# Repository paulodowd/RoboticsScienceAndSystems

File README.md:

# SLAMDunk

Fork of the University of Bristol MSc Robotics "Robotics Science and Systems"
unit repository, containing the digital twin simulation platform and StampC3
robot template code used for coursework/labs on the module, plus our own
tooling for logging and benchmarking the robot.

Course guide: <https://semtm0043-42.github.io/getting-started.html>

## Repository layout

| Path | What it is |
|---|---|
| `StampC3_Template/` | Arduino sketch for the M5Stack StampC3 that controls the Pololu 3Pi+ over I2C and streams telemetry over WiFi |
| `DigitalTwin/` | Processing sketch: simulated robot, live comparison with the real robot |
| `tools/logger.py` | Python telemetry logger: live terminal dashboard and Rerun visualisation |
| `logs/` | Local captures (ignored by git) |
| `TODO.md` | Benchmarking plan for the final project |

## System overview

```
Pololu 3Pi+ (ATmega32U4, course middleware)
        │ I2C, address 0x08
M5Stack StampC3 (ESP32-C3) ── runs StampC3_Template
        │ WiFi access point, TCP 192.168.4.1:80, one client at a time
Laptop ── tools/logger.py  or  DigitalTwin
```

The robot sends one CSV line every 50 ms, in this order (see `StampC3_Template/Controller.h`):

```
t_ms, x_mm, y_mm, theta_rad, pwm_left, pwm_right, enc_left, enc_right, dn1, dn2, dn3, dn4, dn5, signal
```

`t_ms` is the StampC3's uptime. x, y and theta come from the StampC3's own
odometry. dn1–dn5 are the surface sensors. The line thresholds for each sensor should ideally be tuned individually for each individual robot. `signal` is 0 while waiting and 1 once the button has
started the controller.

---

## 1. Robot setup (Arduino)

**All of these instructions can also be found in the course guide (Link above or in your course blackboard). Treat this as distilled information from the course guide.**

### Arduino IDE

Install Arduino IDE 2.x from <https://www.arduino.cc/en/software>.

On Linux, use the **AppImage**, not the snap. The snap is sandboxed and cannot
open files outside your home folder (for example, a repo under `/data`).

```bash
chmod +x arduino-ide_*_Linux_64bit.AppImage
./arduino-ide_*_Linux_64bit.AppImage
```

If it fails to start with a FUSE error, run `sudo apt install libfuse2`.

For macOS and Windows check the course guide for instructions.

### Board package and libraries

1. **File → Preferences → Additional boards manager URLs**, add:
   ```
   https://static-cdn.m5stack.com/resource/arduino/package_m5stack_index.json
   ```
2. **Tools → Board → Boards Manager**: search `M5Stack` and install it.
3. **Tools → Manage Libraries**: install `LSM6` and `LIS3MDL` (both by Pololu).

### Flashing

1. Open `StampC3_Template/StampC3_Template.ino`.
2. Tools settings:
   - **Board:** M5Stack Arduino → **M5StampC3**
   - **USB CDC On Boot:** **Disabled** (otherwise the Serial Monitor shows nothing)
   - **Upload Speed:** 921600, or 115200 if uploads fail
3. **Set a unique WiFi name and password** on this line of the sketch:
   ```cpp
   RobotWifiAP_c server("myAP", "myPassword", 80);
   ```
   Every robot running the template broadcasts `myAP` by default, so in a lab
   you could end up connected to someone else's robot.
4. Upload, then turn the 3Pi+ on with its power button.

The Serial Monitor runs at **115200 baud** and shows the same CSV lines as WiFi.

### Serial port access (Linux)

Your user must be in the `dialout` group to upload over USB:

```bash
sudo usermod -aG dialout $USER     # then log out and back in
```

### Batteries

Use 4 × AA NiMH cells, fully charged; wait until every charger channel shows
green. **Motor speed at a fixed PWM drops as the batteries run down, which
affects tuning and odometry. Note the charge state in any benchmark.**

---

## 2. Digital Twin (Processing)

1. Install Processing 4 from <https://processing.org/download>.
2. Open `DigitalTwin/DigitalTwin.pde`.
3. Run it. It works standalone as a simulator. For live comparison it connects
   to the robot at `192.168.4.1:80` (set in `DigitalTwin/Simulator.pde`).

The robot serves only **one TCP client**, so the Digital Twin and the logger
cannot both be connected over WiFi at the same time.

---

## 3. Telemetry logger (`tools/logger.py`)

### Install

The logger needs **Python 3.10 or newer** and two packages:

- `rich` draws the live terminal dashboard.
- `rerun-sdk` includes the Rerun viewer (the `rerun` command). Tested with
  rerun-sdk 0.27.2. Rerun's API changes between releases, so if a newer
  version breaks something, install that version instead: `rerun-sdk==0.27.2`.

Install them in a **virtual environment** (`.venv`, a private folder of
packages for this project). Newer Linux distributions and Homebrew Python
refuse `pip install` outside one, and it keeps the versions separate from
the rest of your system. Run these from the repo's root folder.

#### Linux (Ubuntu/Debian)

```bash
sudo apt install python3 python3-venv python3-pip
python3 -m venv .venv
source .venv/bin/activate
pip install rich rerun-sdk
```

#### macOS

Install Python 3 from <https://www.python.org/downloads/> or with Homebrew
(`brew install python`). The `python3` that comes with Xcode's command line
tools may be older than 3.10; check with `python3 --version`.

```bash
python3 -m venv .venv
source .venv/bin/activate
pip install rich rerun-sdk
```

#### Windows

Install Python 3 from <https://www.python.org/downloads/> and tick
**"Add python.exe to PATH"** in the installer, or run
`winget install Python.Python.3.12`. Use Windows Terminal (PowerShell) so the
dashboard draws correctly.

```powershell
py -m venv .venv
.venv\Scripts\Activate.ps1
pip install rich rerun-sdk
```

If PowerShell refuses to run `Activate.ps1`, allow local scripts once with
`Set-ExecutionPolicy -Scope CurrentUser RemoteSigned`, then try again. In
Command Prompt (cmd) the activate command is `.venv\Scripts\activate.bat`.

#### Check the install

With the virtual environment active (your prompt starts with `(.venv)`):

```bash
python -c "import rich, rerun; print('ok', rerun.__version__)"
```

Activate the environment again (`source .venv/bin/activate`, or
`.venv\Scripts\Activate.ps1` on Windows) in each new terminal before running
the logger. `.venv/` is ignored by git.

### Connect to the robot

The robot is its own WiFi network. Join it with the name and password you set
in the sketch. While connected, your computer has no internet over WiFi.

You can connect to the the robot like you connect to a normal wifi network, or follow the commands below to connect from terminal.

**Linux:**

```bash
nmcli dev wifi connect <robot-ssid> password <robot-password>
```

To stop NetworkManager switching back to a network with internet in the
middle of a run, give the robot's network priority:

```bash
nmcli con modify <robot-ssid> connection.autoconnect-priority 100
```

**macOS:** choose the network from the WiFi menu in the menu bar, or:

```bash
networksetup -setairportnetwork en0 <robot-ssid> <robot-password>
```

(`en0` is the WiFi interface on most Macs; `networksetup -listallhardwareports`
shows yours.) macOS may warn that the network has no internet connection;
stay connected anyway.

**Windows:** choose the network from the WiFi icon in the taskbar. When
Windows reports "No internet", stay connected anyway. If Windows asks whether
to allow Python or Rerun through the firewall, allow it on private networks.

**Check that data is arriving** (all platforms, `Ctrl+C` to stop):

```bash
python -c "import socket; s=socket.create_connection(('192.168.4.1',80)); [print(d.decode(), end='') for d in iter(lambda: s.recv(4096), b'')]"
```

On Linux and macOS, `nc 192.168.4.1 80` does the same.

### Run

Settings are constants at the top of `tools/logger.py`:

| Constant | Robot | Local test | Meaning |
|---|---|---|---|
| `HOST` | `"192.168.4.1"` | `"127.0.0.1"` | Address to connect to |
| `PORT` | `80` | `9000` | TCP port |
| `TIMEOUT_S` | `3` | `3` | Seconds of silence before giving up |
| `USE_RERUN` | `True` | `True` | Open the Rerun viewer |

Then, with the virtual environment active:

```bash
python tools/logger.py            # Linux, macOS
```

```powershell
python tools\logger.py            # Windows
```

Stop it with **Ctrl+C**.

The first time the Rerun viewer opens, macOS or Windows may ask whether to
allow incoming network connections. Allow it: the logger sends data to the
viewer over a local network port.

### What you see

**Terminal:** a table of the latest record with every field labelled, updated
about 10 times a second. Warnings and errors are printed above the table.

**Rerun viewer** (opens automatically when `USE_RERUN = True`):

| Panel | Shows |
|---|---|
| Path | The robot's trail and a heading arrow (odometry x, y, theta) |
| Pose | x, y, theta over time |
| Motor PWM | Commanded left and right PWM |
| Encoders | Left and right encoder counts |
| Surface sensors | dn1–dn5 over time |
| Surface now | Bar chart of the current dn1–dn5 |

Notes on the viewer:

- The time axis is the robot's own clock (`robot_time`), so WiFi delays don't
  distort the plots. Drag the time cursor to scrub back through a run.
- The Path view draws y flipped, because Rerun's 2D +y points down and the
  robot's +y is anticlockwise (up). The Pose plots show the true y.
- If a viewer is already open, the logger adds a new recording to it rather
  than opening a second window. Pick recordings from the list on the left.
- After a robot reset, `t_ms` restarts near 0, so the new data is drawn over
  the old run on the same timeline.
- Without a display (for example, over SSH) the viewer cannot open. Set
  `USE_RERUN = False`.

### Log messages

| Message | Meaning |
|---|---|
| `not on the robot's WiFi` | The laptop has no route to 192.168.4.1. Join the robot's network. |
| `Server not listening. Robot must be booting.` | Something answered, but nothing is listening on the port. Wait for the robot to finish booting, or check `nc` is running for a local test. |
| `robot did not answer within 3 s` | No answer to the connection at all: robot off or out of range. |
| `no data for 3 s` | Connected, but the data stopped: robot reset, out of range, laptop left the network, or another client holds the connection. |
| `connection ended: Closed by the server.` | The other side closed the connection normally. |
| `expected 14 fields, got N` / `not a number` | A line that isn't a telemetry record was received and skipped. |
| `discarding incomplete last line` | The connection ended partway through a line. |

### Test without the robot

The logger can be tested entirely on your computer, using a saved capture and
a small server pretending to be the robot. No robot or robot WiFi is needed.
These commands work on Linux, macOS and Windows (on Windows, use `\` instead of
`/` in the file paths if a command can't find the file).

1. Record a capture once, while connected to the robot. Press `Ctrl+C` after a
   few seconds; the traceback it prints is expected.
   ```bash
   python -c "import socket; s=socket.create_connection(('192.168.4.1',80)); f=open('logs/capture.csv','wb'); [f.write(d) for d in iter(lambda: s.recv(4096), b'')]"
   ```
2. Set `HOST = "127.0.0.1"` and `PORT = 9000` in `tools/logger.py`.
3. In one terminal, serve the capture:
   ```bash
   python -c "import socket,sys; s=socket.create_server(('127.0.0.1',9000)); c,_=s.accept(); c.sendall(open(sys.argv[1],'rb').read()); c.close()" logs/capture.csv
   ```
4. In another terminal, run the logger:
   ```bash
   python tools/logger.py
   ```

The server exits after one connection, so rerun step 3 before each test. It
closes the connection after sending the file, so the logger should end with
`connection ended: Closed by the server.`

On Linux, `nc` does the same jobs: `nc 192.168.4.1 80 | tee logs/capture.csv`
to record, and `nc -N -l 9000 < logs/capture.csv` to serve (`-N` closes the
connection at the end of the file).

### Current limitations

- **Records are not saved to disk yet.** The dashboard and Rerun show live data
  only. Writing to CSV is the next step. Until then, record a raw capture as
  in step 1 of "Test without the robot".
- **No automatic reconnect.** The logger exits when the connection drops.
  Restart it after the robot resets.
- **One client at a time.** While the logger is connected, the Digital Twin
  (or a second logger) will connect but receive nothing.

---

## Troubleshooting

| Problem | Fix |
|---|---|
| Arduino IDE can't see the repo folder | You're using the snap version. Install the AppImage (see above). |
| Serial Monitor is blank | Set **USB CDC On Boot → Disabled** and re-upload; check the baud rate is 115200. |
| Upload fails or port not found | Add yourself to `dialout`; try Upload Speed 115200. |
| Robot doesn't turn on | Press the 3Pi+ power button; check the cells' orientation and charge. |
| Robot's WiFi doesn't appear | Robot is off, still booting, or the sketch isn't flashed. |
| Logger connects, then exits with `no data for 3 s` | Another client (Digital Twin, `nc`, another logger) may hold the connection. Close it, wait a few seconds, and try again. |
| `ModuleNotFoundError: rich` or `rerun` | The virtual environment isn't active in this terminal. Activate it (see Install), or install the packages into it. |
| `error: externally-managed-environment` from pip | You ran pip outside the virtual environment. Create and activate `.venv` first (see Install). |
| Windows: `python` opens the Microsoft Store or isn't found | Use `py` instead of `python`, or reinstall Python with "Add python.exe to PATH" ticked. |
| Windows: `Activate.ps1 cannot be loaded` | Run `Set-ExecutionPolicy -Scope CurrentUser RemoteSigned` once in PowerShell. |
| Logger says `robot did not answer` instead of `not on the robot's WiFi` | Normal on some systems when you aren't on the robot's network: the connection times out instead of failing straight away. Check which WiFi you're on. |
| Rerun viewer doesn't open (macOS/Windows) | Allow the firewall or "incoming connections" prompt, then run the logger again. |

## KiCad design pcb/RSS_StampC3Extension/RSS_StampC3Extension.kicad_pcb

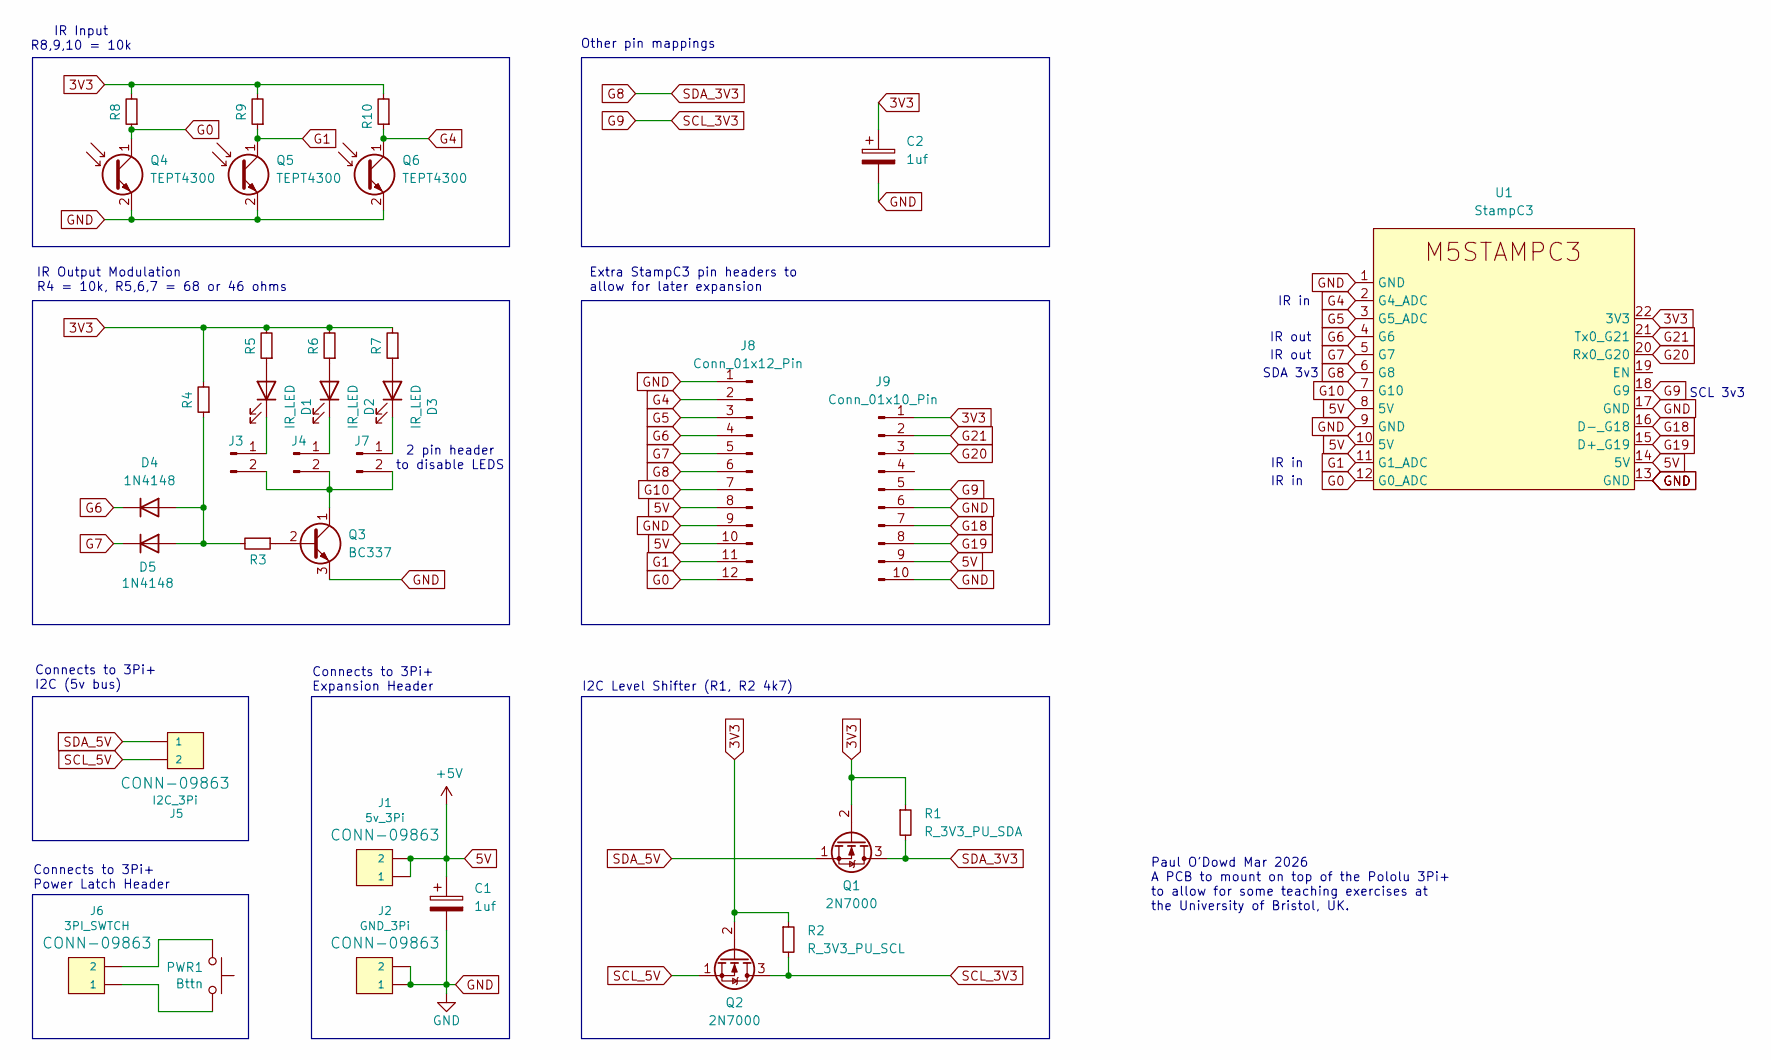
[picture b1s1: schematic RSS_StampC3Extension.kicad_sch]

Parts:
C1, C2: 1uf; CP_Radial_D5.0mm_P2.00mm
D1, D2, D3: IR_LED; LED_D3.0mm_Horizontal_O1.27mm_Z2.0mm
D4, D5: 1N4148; D_DO-35_SOD27_P7.62mm_Horizontal
J1: 5v_3Pi; PinHeader_1x02_P2.54mm_Vertical
J2: GND_3Pi; PinHeader_1x02_P2.54mm_Vertical
J3, J4, J7: PinHeader_1x02_P2.54mm_Vertical
J5: I2C_3Pi; PinHeader_1x02_P2.54mm_Vertical
J6: 3PI_SWTCH; PinHeader_1x02_P2.54mm_Vertical
J8: Conn_01x12_Pin; PinHeader_1x12_P2.54mm_Vertical
J9: Conn_01x10_Pin; PinHeader_1x10_P2.54mm_Vertical
PWR1: Bttn; SW_PUSH_6mm
Q1, Q2: 2N7000; TO-92_Inline
Q3: BC337; TO-92_Inline
Q4, Q5, Q6: TEPT4300; LED_D3.0mm_Clear
R1: R_3V3_PU_SDA; R_Axial_DIN0207_L6.3mm_D2.5mm_P10.16mm_Horizontal
R2: R_3V3_PU_SCL; R_Axial_DIN0207_L6.3mm_D2.5mm_P10.16mm_Horizontal
R3, R4, R5, R6, R7, R8, R9, R10: R_Axial_DIN0207_L6.3mm_D2.5mm_P10.16mm_Horizontal
U1: StampC3; Stamp-C3

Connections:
3V3: C2.1, J9.1, Q1.2 (G), Q2.2 (G), R1.1, R2.1, R4.2, R5.2, R6.2, R7.2, R8.2, R9.2, R10.2, U1.22 (3V3)
5V: C1.1, J1.1, J1.2, J8.8, J8.10, J9.9, U1.8 (5V), U1.10 (5V), U1.14 (5V)
G0: J8.12, Q4.1 (C), R8.1, U1.12 (G0_ADC)
G1: J8.11, Q5.1 (C), R9.1, U1.11 (G1_ADC)
G4: J8.2, Q6.1 (C), R10.1, U1.2 (G4_ADC)
G5: J8.3, U1.3 (G5_ADC)
G6: D4.1 (K), J8.4, U1.4 (G6)
G7: D5.1 (K), J8.5, U1.5 (G7)
G8: J8.6, Q1.3 (D), R1.2, U1.6 (G8)
G9: J9.5, Q2.3 (D), R2.2, U1.18 (G9)
G10: J8.7, U1.7 (G10)
G18: J9.7, U1.16 (D-_G18)
G19: J9.8, U1.15 (D+_G19)
G20: J9.3, U1.20 (Rx0_G20)
G21: J9.2, U1.21 (Tx0_G21)
GND: C1.2, C2.2, J2.1, J2.2, J8.1, J8.9, J9.6, J9.10, Q3.3 (E), Q4.2 (E), Q5.2 (E), Q6.2 (E), U1.1 (GND), U1.9 (GND), U1.13 (GND), U1.17 (GND)
unnamed: D1.2 (A), R5.1
unnamed: D1.1 (K), J3.1
unnamed: D2.2 (A), R6.1
unnamed: D2.1 (K), J4.1
unnamed: D3.2 (A), R7.1
unnamed: D3.1 (K), J7.1
unnamed: D4.2 (A), D5.2 (A), R3.2, R4.1
unnamed: J3.2, J4.2, J7.2, Q3.1 (C)
unnamed: J6.1, PWR1.1
unnamed: J6.2, PWR1.2
unnamed: Q3.2 (B), R3.1
SCL_5V: J5.2, Q2.1 (S)
SDA_5V: J5.1, Q1.1 (S)

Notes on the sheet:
IR out
IR in
2 pin header to disable LEDS
Paul O'Dowd Mar 2026 A PCB to mount on top of the Pololu 3Pi+ to allow for some teaching exercises at the University of Bristol, UK.
IR Input R8,9,10 = 10k
I2C Level Shifter (R1, R2 4k7)
IR Output Modulation R4 = 10k, R5,6,7 = 68 or 46 ohms
Connects to 3Pi+ I2C (5v bus)
Extra StampC3 pin headers to allow for later expansion
Connects to 3Pi+ Expansion Header
SDA 3v3
SCL 3v3
Connects to 3Pi+ Power Latch Header
Other pin mappings

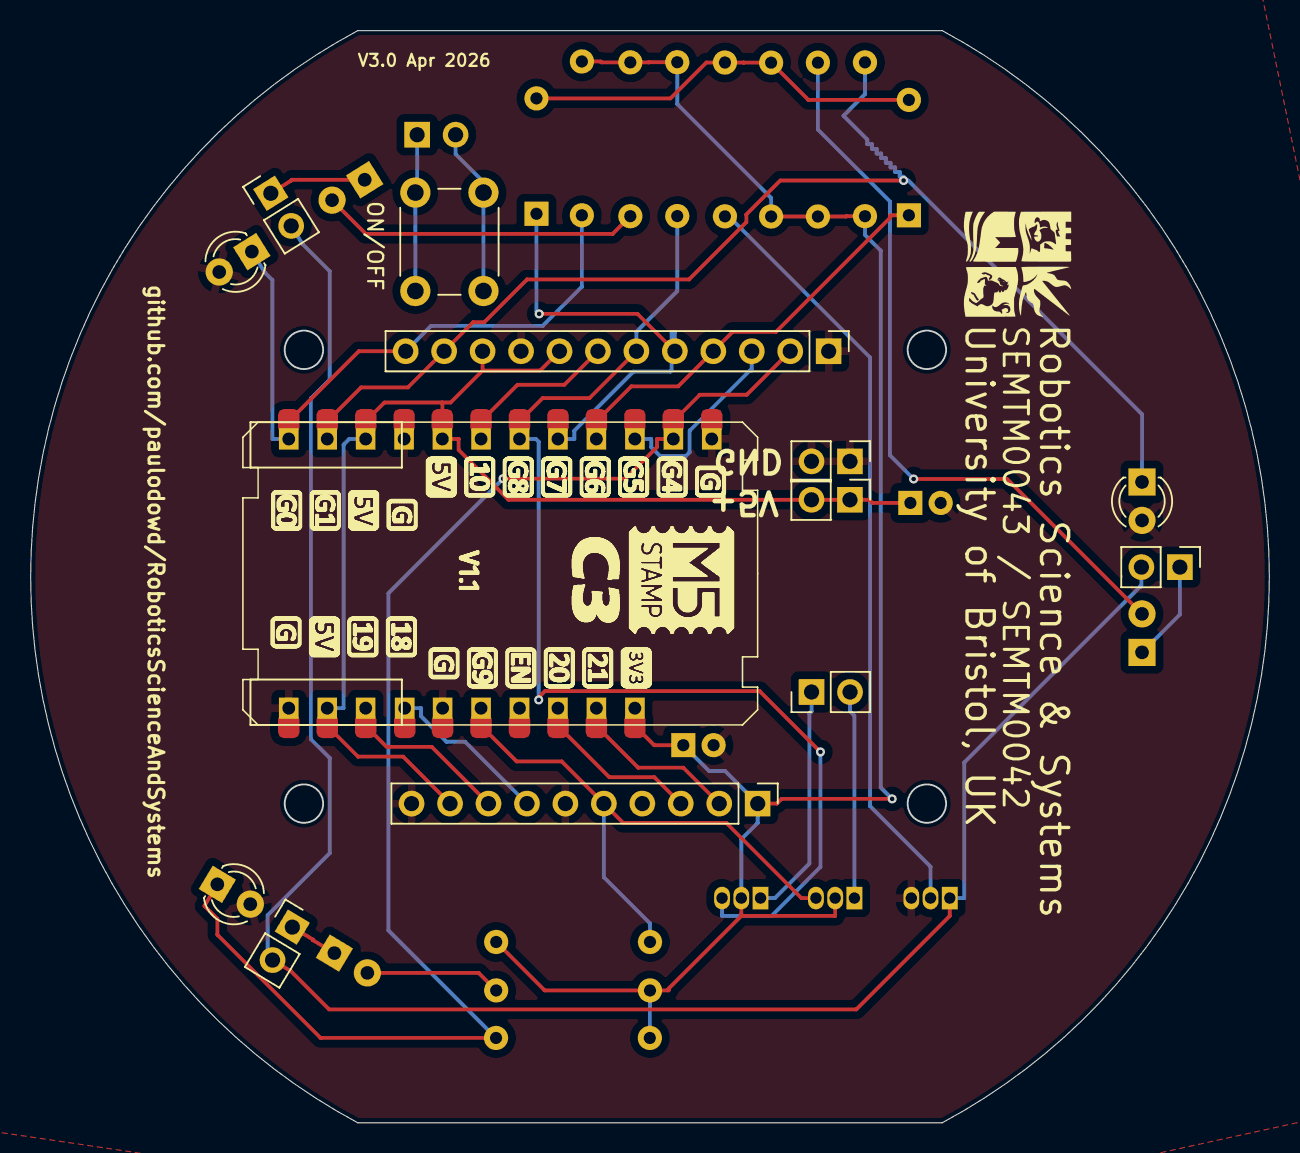
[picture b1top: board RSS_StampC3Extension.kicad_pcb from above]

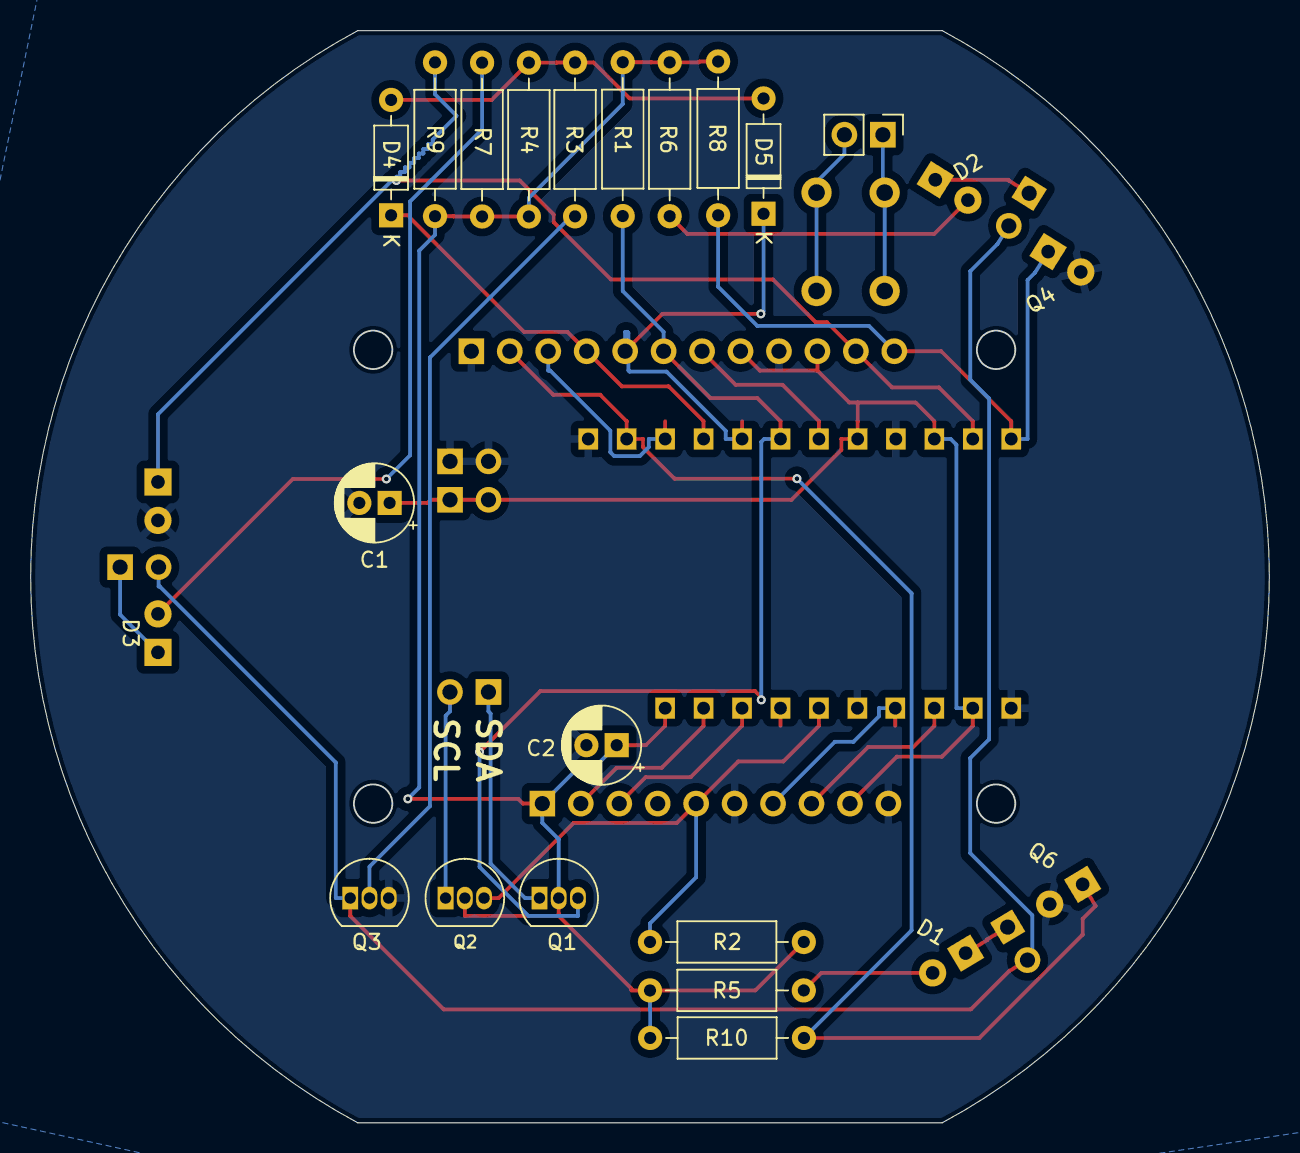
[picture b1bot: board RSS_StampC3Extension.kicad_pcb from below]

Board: 2 copper layers, 81.8 x 72.1 mm, 34 parts (18 on the bottom side), 29 nets.

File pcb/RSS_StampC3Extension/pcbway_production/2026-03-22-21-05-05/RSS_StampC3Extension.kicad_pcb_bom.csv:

Designator,Quantity,Value,Footprint,Package,MPN,DNP,Mount_Type,Description,Sim.Device,Sim.Pins,Field4
"D1, D2, D3",3,IR_LED,LED_D3.0mm_Horizontal_O1.27mm_Z2.0mm,,,,tht,,,,
"D4, D5",2,1N4148,D_DO-35_SOD27_P7.62mm_Horizontal,,,,tht,"100V 0.15A standard switching diode, DO-35",D,1=K 2=A,
J1,1,5v_3Pi,PinHeader_1x02_P2.54mm_Vertical,,,,tht,,,,CONN-09863
J2,1,GND_3Pi,PinHeader_1x02_P2.54mm_Vertical,,,,tht,,,,CONN-09863
J5,1,I2C_3Pi,PinHeader_1x02_P2.54mm_Vertical,,,,tht,,,,CONN-09863
J6,1,3PI_SWTCH,PinHeader_1x02_P2.54mm_Vertical,,,,tht,,,,CONN-09863
J8,1,Conn_01x12_Pin,PinHeader_1x12_P2.54mm_Vertical,,,,tht,,,,
J9,1,Conn_01x10_Pin,PinHeader_1x10_P2.54mm_Vertical,,,,tht,,,,
PWR1,1,Bttn,SW_PUSH_6mm,,,,tht,,,,
"Q1, Q2",2,2N7000,TO-92_Inline,,,,tht,,,,
Q3,1,BC337,TO-92_Inline,,,,tht,"0.8A Ic, 45V Vce, NPN Transistor, TO-92",,,
"Q4, Q5, Q6",3,TEPT4300,LED_D3.0mm_Clear,,,,tht,"Ambient Light Sensor, NPN Epitaxial Planar Phototransistor, T-1",,,
R1,1,R_3V3_PU_SDA,R_Axial_DIN0207_L6.3mm_D2.5mm_P10.16mm_Horizontal,,,,tht,,,,
"R10, R3, R4, R5, R6, R7, R8, R9",8,~,R_Axial_DIN0207_L6.3mm_D2.5mm_P10.16mm_Horizontal,,,,tht,,,,
R2,1,R_3V3_PU_SCL,R_Axial_DIN0207_L6.3mm_D2.5mm_P10.16mm_Horizontal,,,,tht,,,,
U1,1,StampC3,Stamp-C3,,,,tht,Module M5Stack Stamp-C3,,,

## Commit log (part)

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2026-03-24 testing commit
2026-03-24 adding pcb design files before first manufacture
2026-03-24 adding development diary to readme
2026-03-24 adding latest pcb build files
2026-03-24 updated readme with a note for grbl file location
2026-03-24 adding some working code to operate the board, and attribution and license to freenove_ws2812_Lib_for_ESP32 library
2026-04-04 Fixed missing connections between phototransistors and GPIO0,1,4 in schematic. Also, GPIO 5 cannot be used for ADC when using Wifi. So moved previous connection from GPIO 5 to 4. Added bigger text to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
2026-04-13 Added a decoupling transistor, adjusted some text and added logo to silkscreen. Should be ready for production.
2026-04-13 devlog update to readme
